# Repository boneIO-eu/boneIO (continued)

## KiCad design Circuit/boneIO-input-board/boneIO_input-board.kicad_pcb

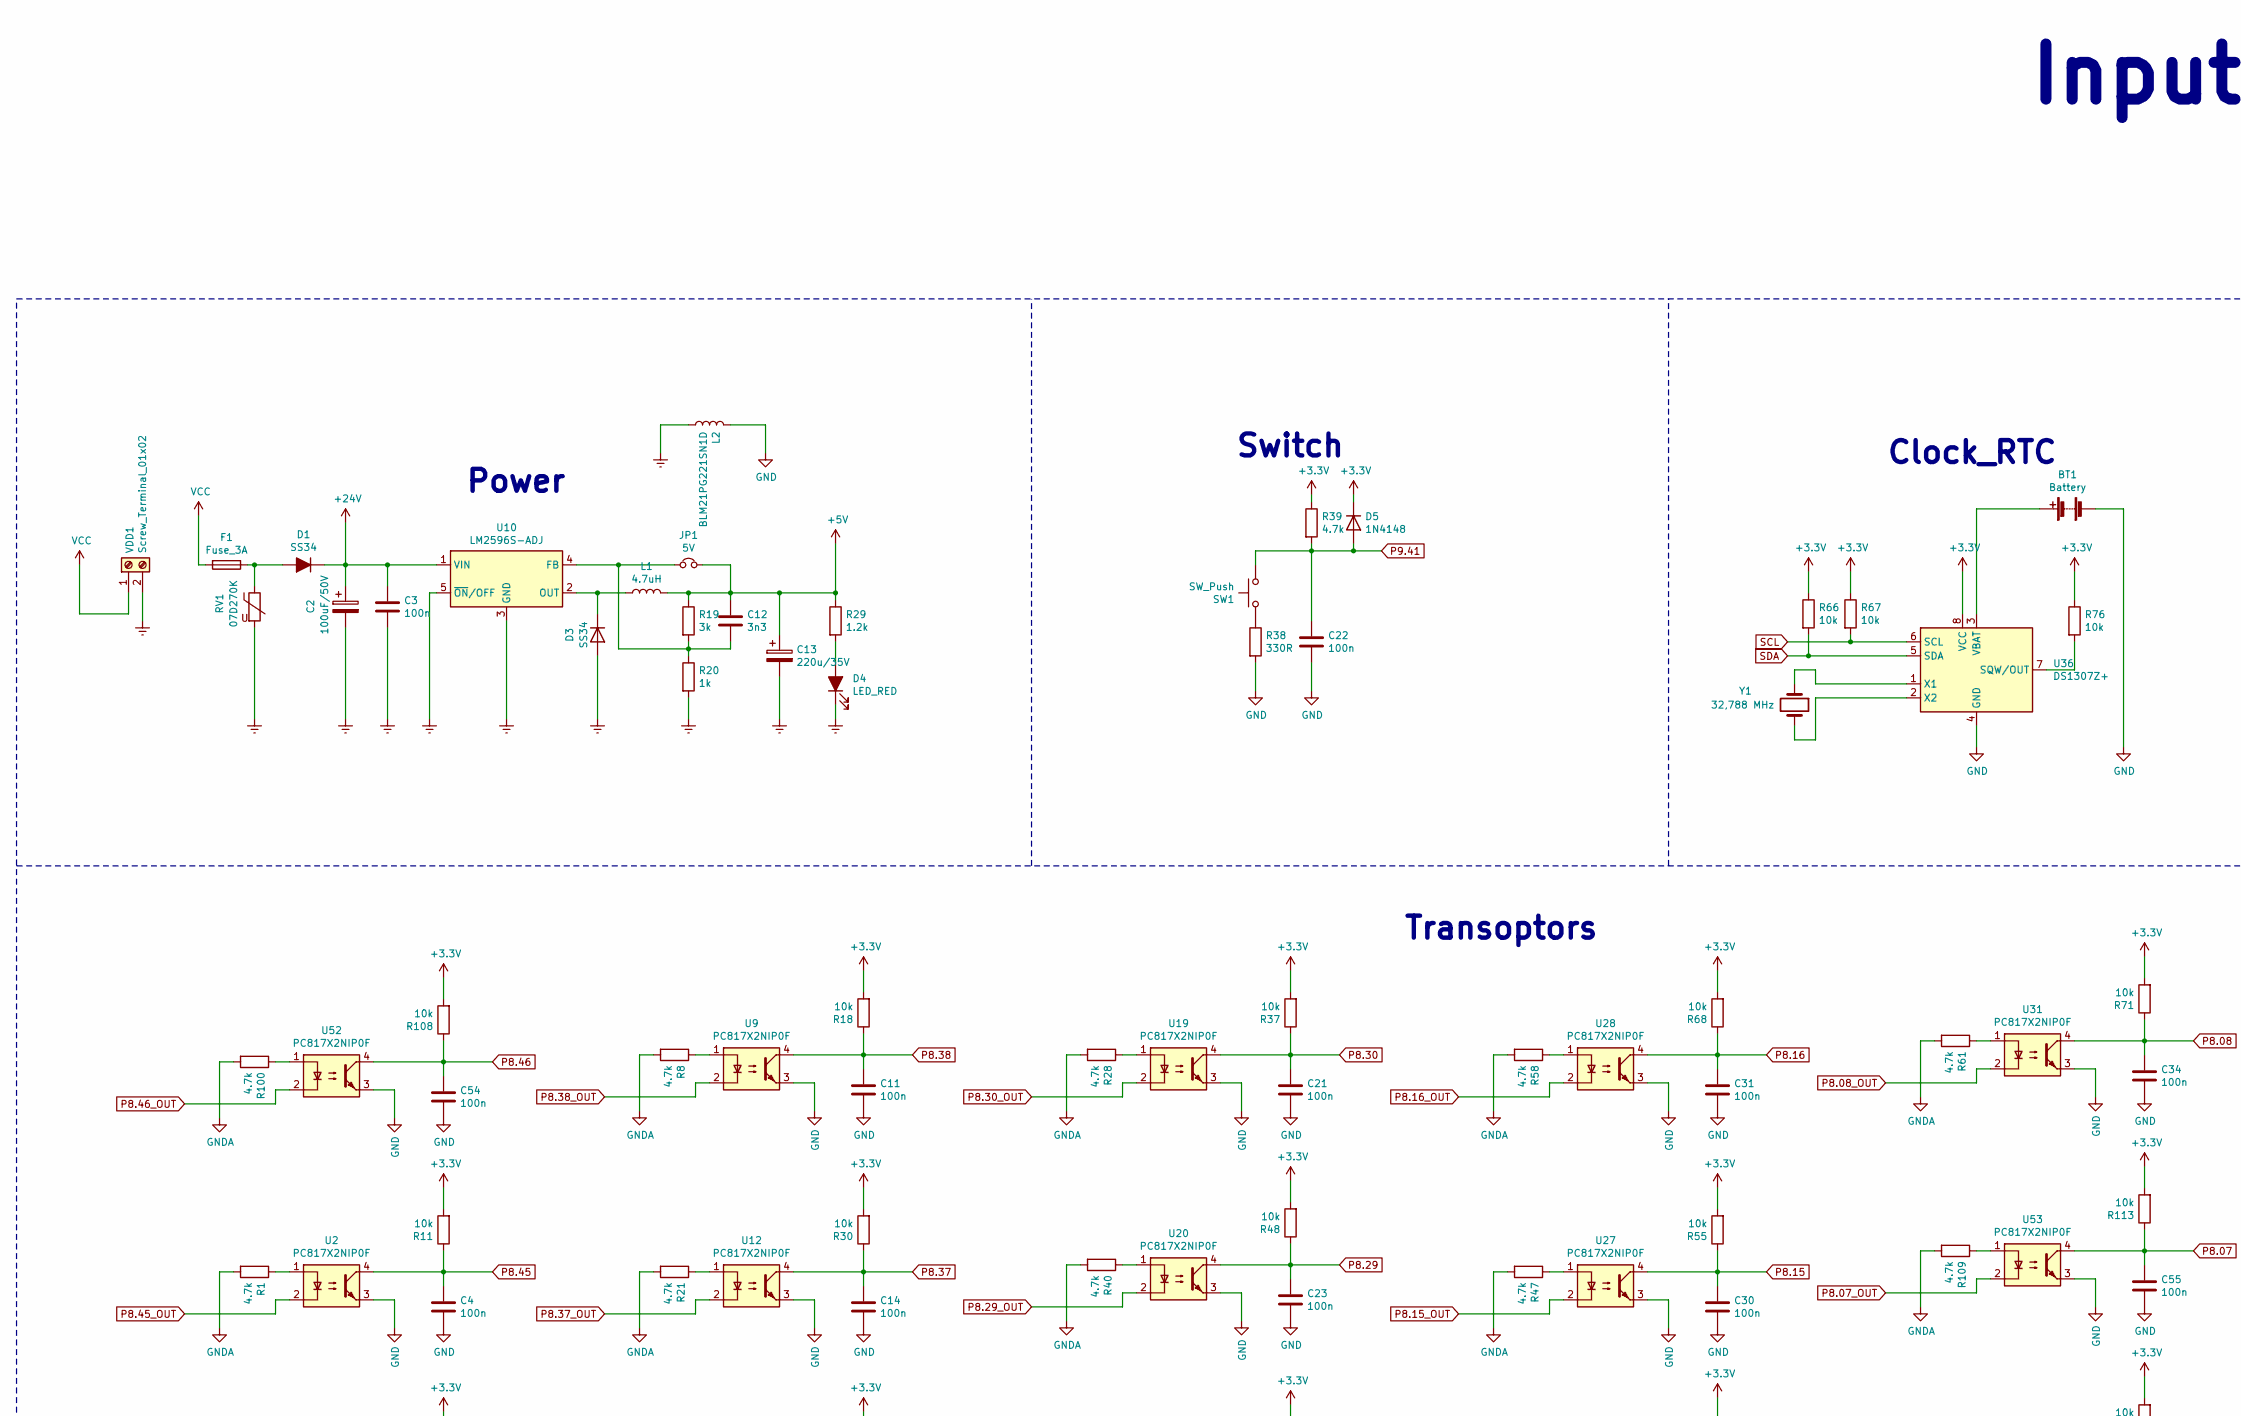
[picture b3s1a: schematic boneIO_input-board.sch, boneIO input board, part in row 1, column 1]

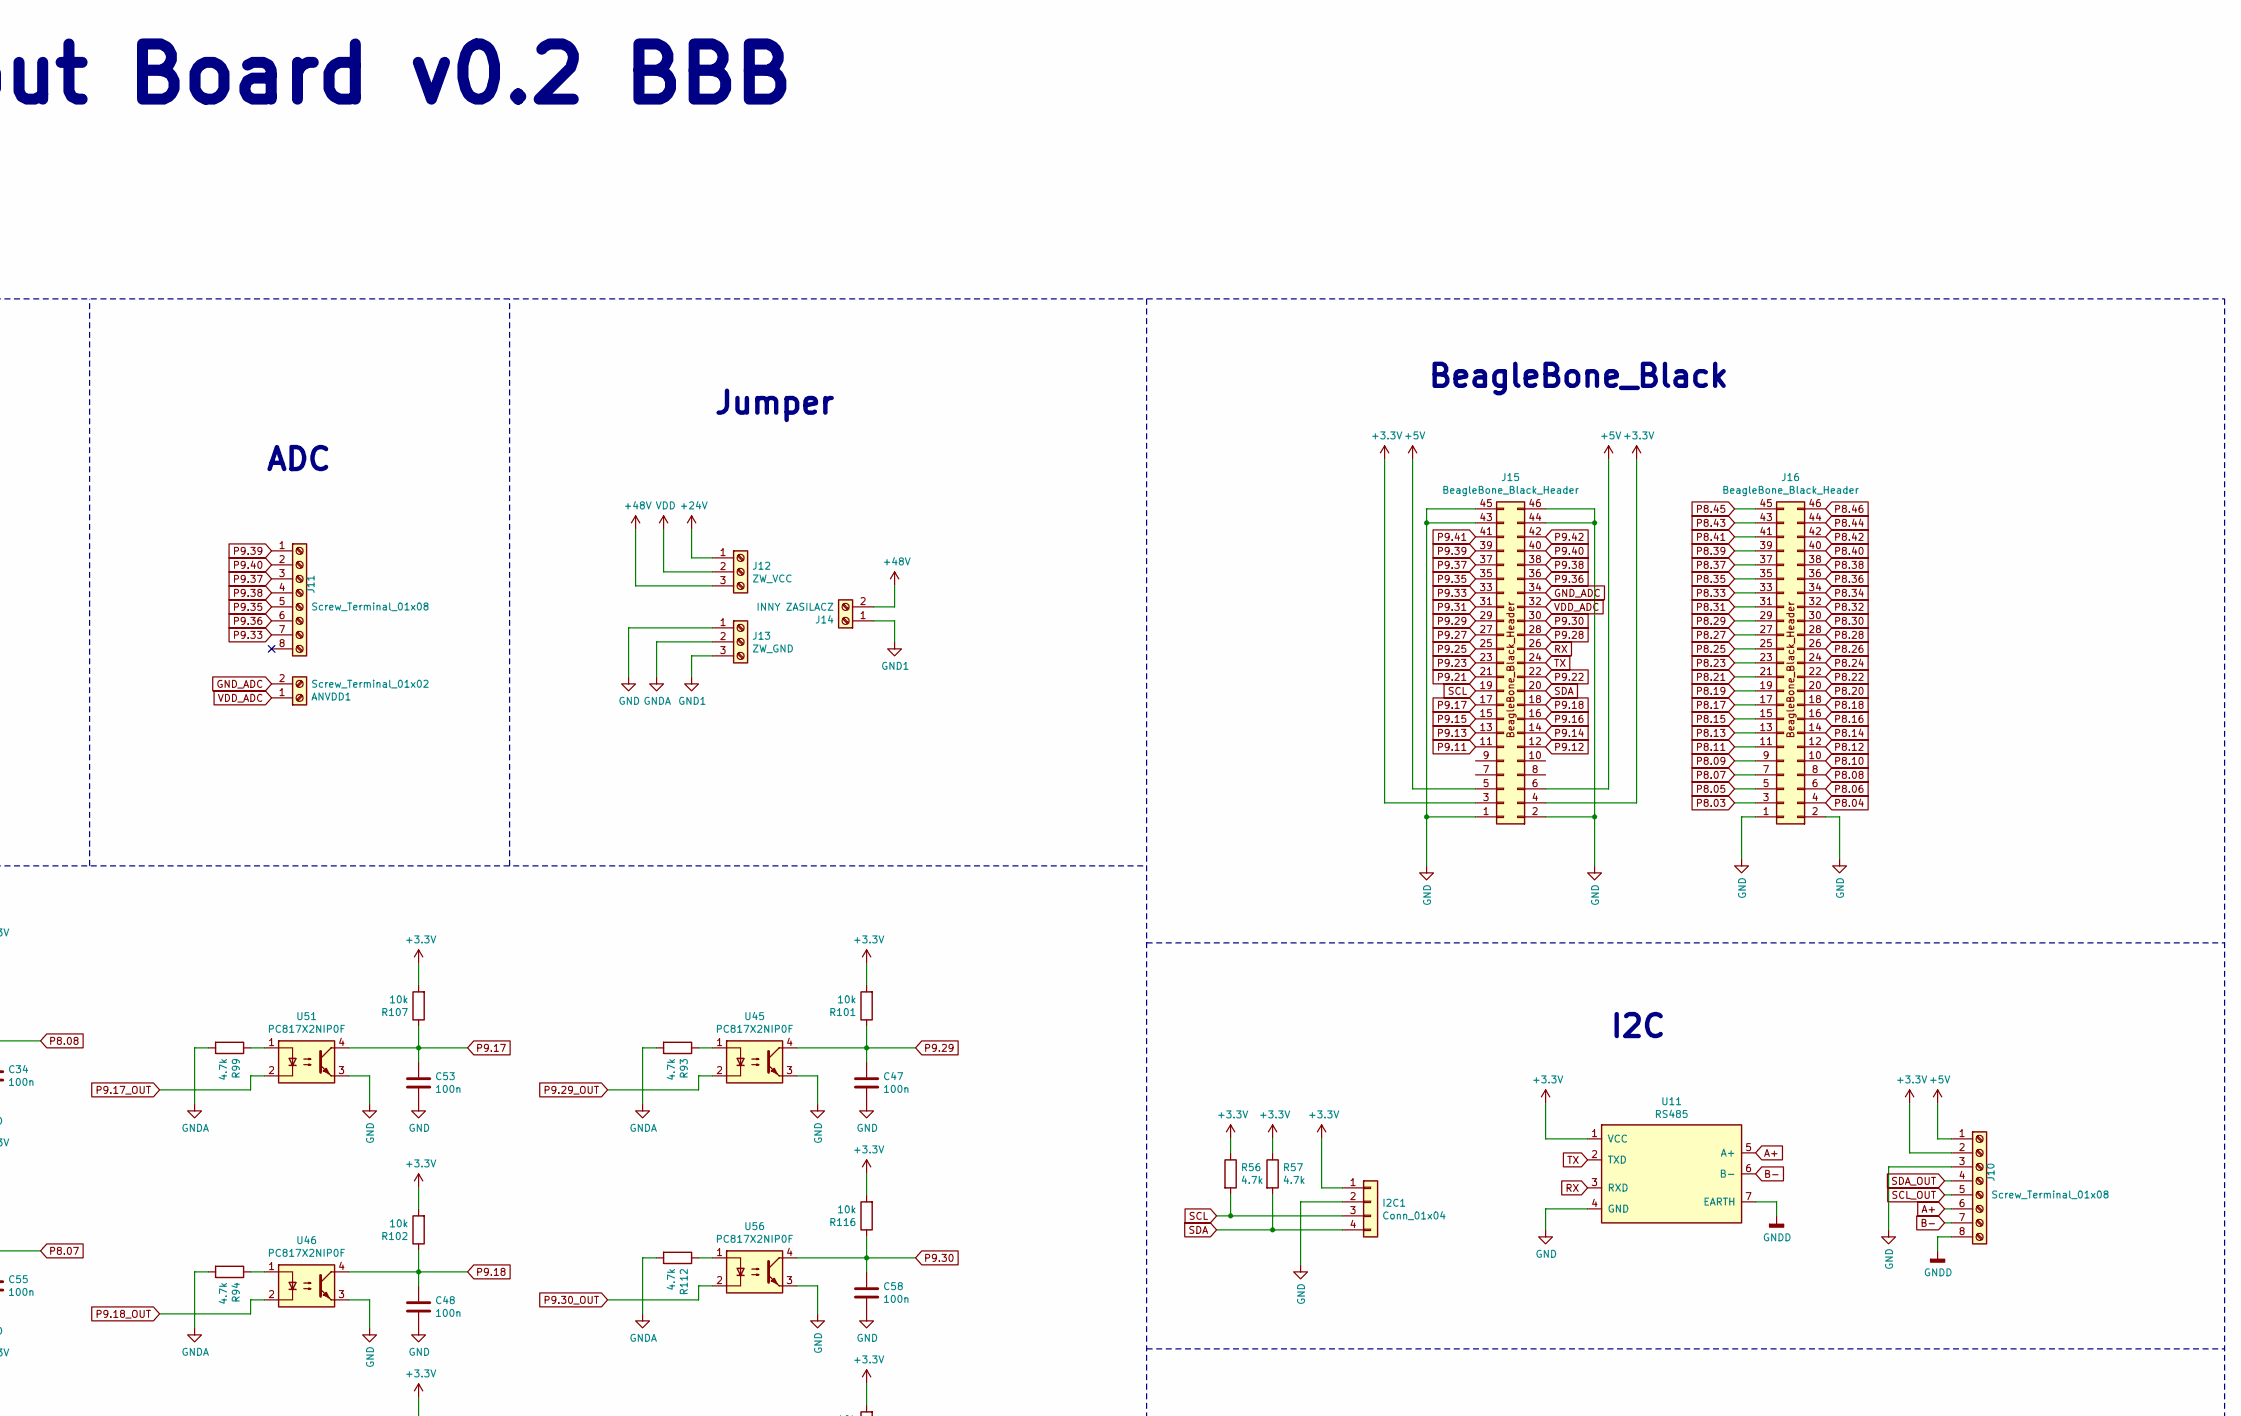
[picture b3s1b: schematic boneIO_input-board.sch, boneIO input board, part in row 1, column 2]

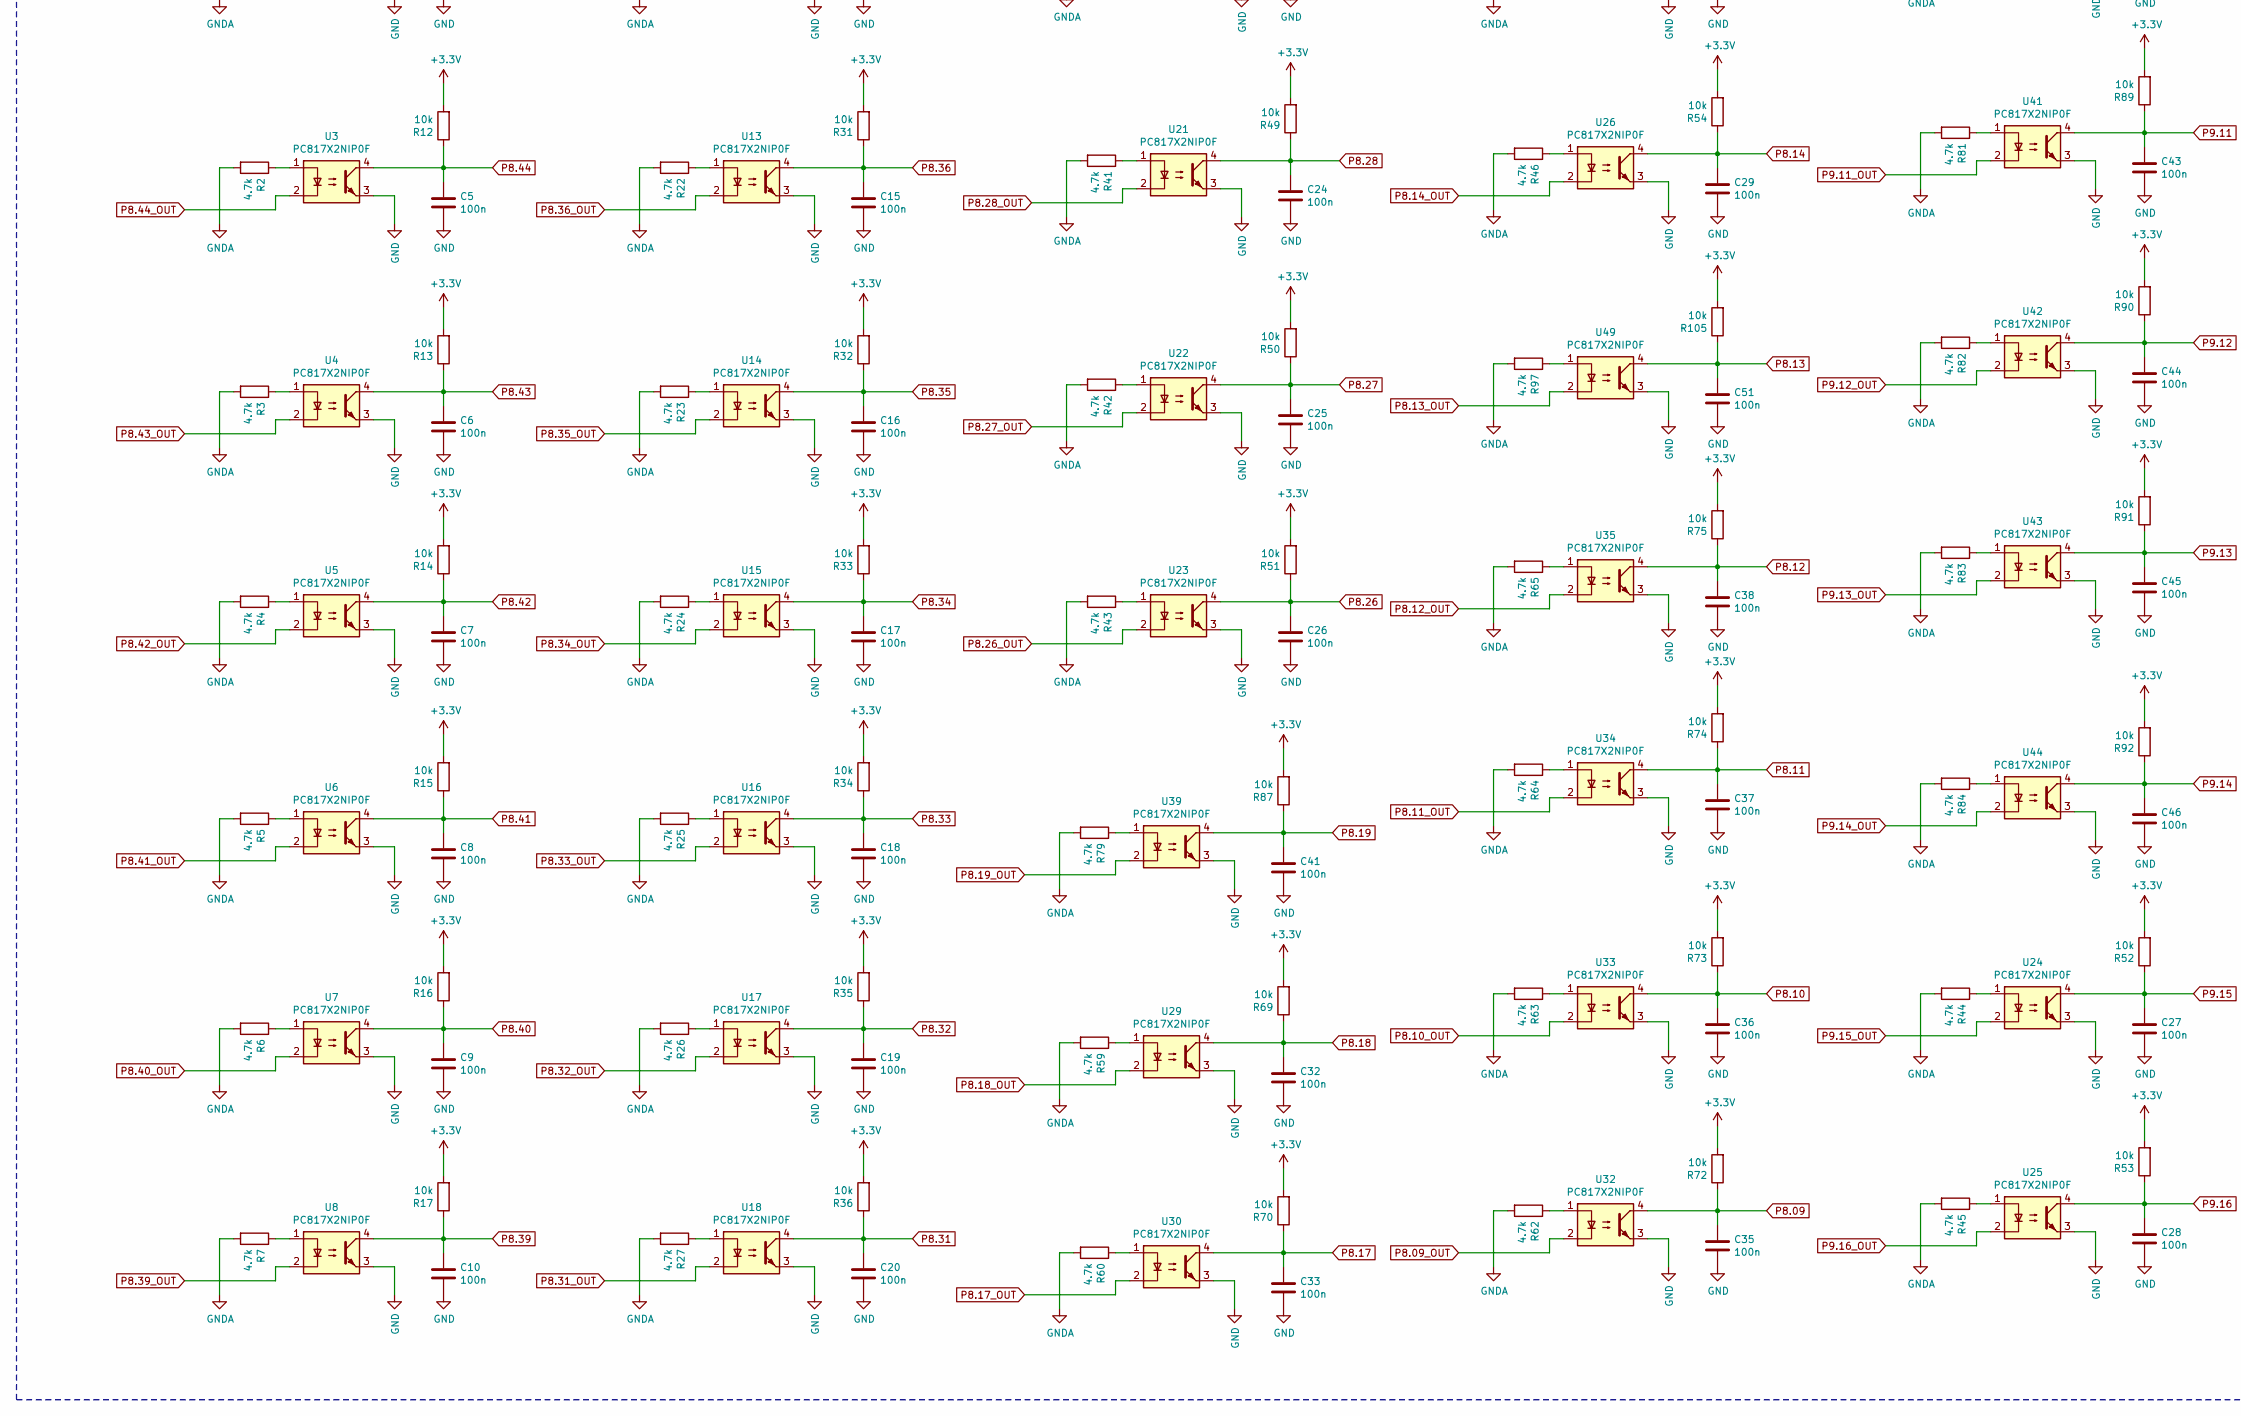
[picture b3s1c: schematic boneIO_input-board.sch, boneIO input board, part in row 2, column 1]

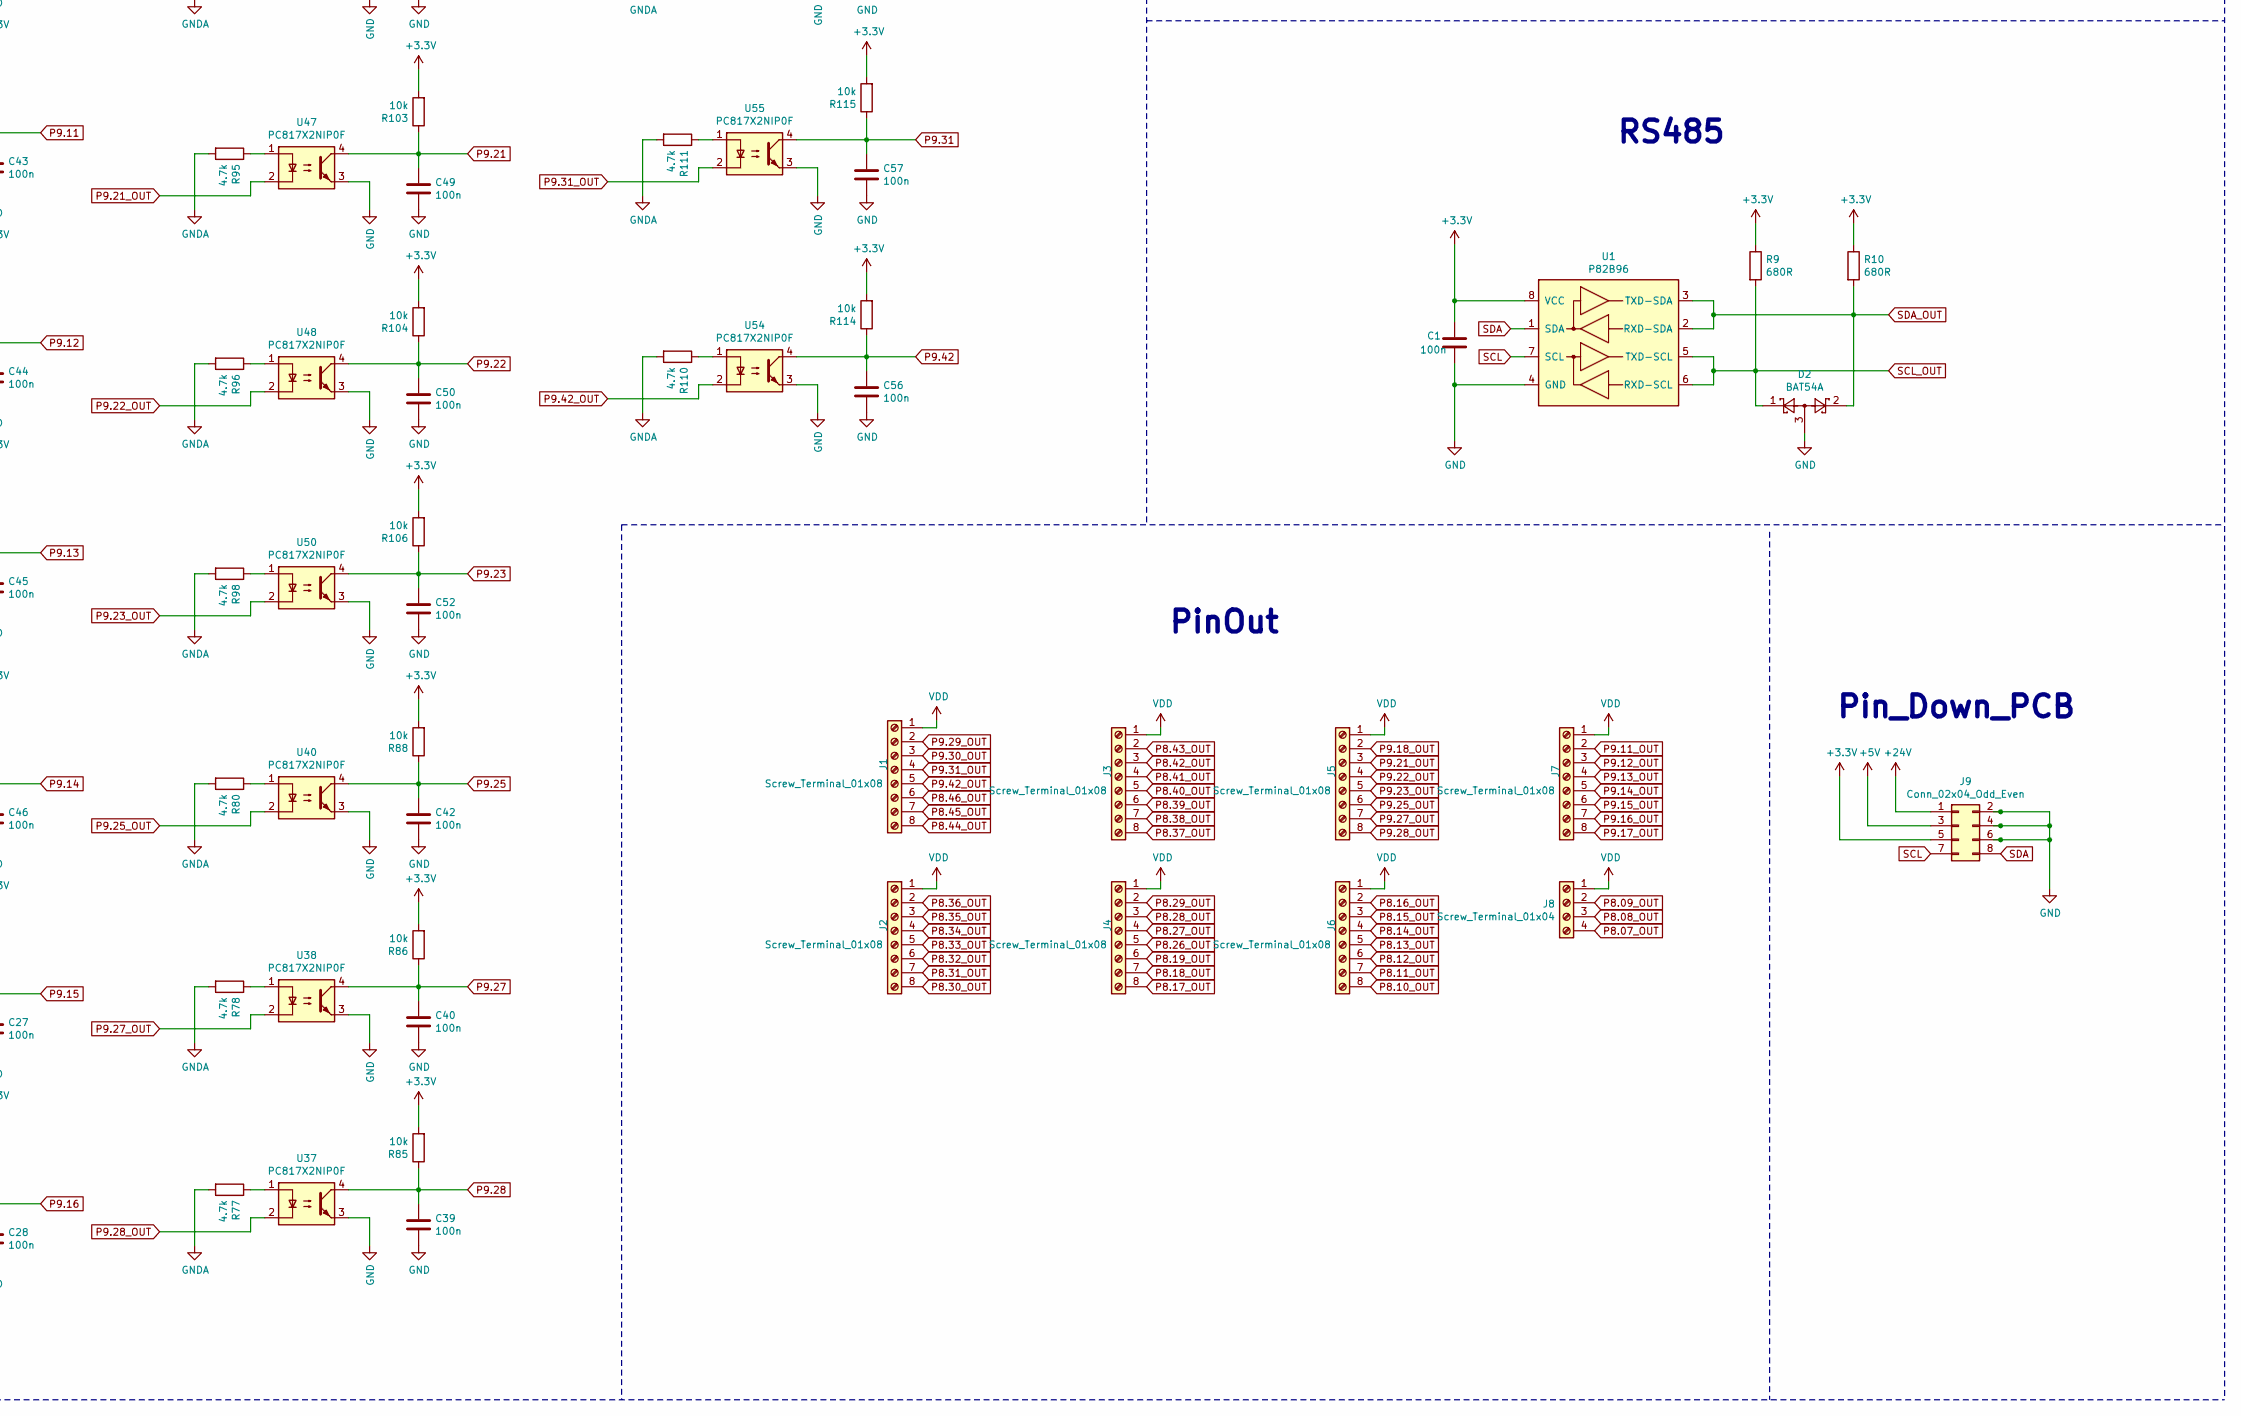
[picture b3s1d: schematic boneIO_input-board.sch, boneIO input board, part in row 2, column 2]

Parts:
ANVDD1: Screw_Terminal_01x02; Phoenix_1x02_P5.00mm_Horizontal
BT1: Battery; Battery_Panasonic_CR1220-VCN_Vertical_CircularHoles
C1, C3, C4, C5, C6, C7, C8, C9, C10, C11, C14, C15, C16, C17, C18, C19, C20, C21, C22, C23, C24, C25, C26, C27, C28, C29, C30, C31, C32, C33, C34, C35, C36, C37, C38, C39, C40, C41, C42, C43, C44, C45, C46, C47, C48, C49, C50, C51, C52, C53, C54, C55, C56, C57, C58: 100n; C_0603_1608Metric; JLCPCB C14663
C2: 100uF/50V; CP_Elec_8x10; JLCPCB C72480
C12: 3n3; C_0805_2012Metric; JLCPCB C107149
C13: 220u/35V; CP_Elec_8x10; JLCPCB C311611
D1: SS34; D_SMA; JLCPCB C64982
D2: BAT54A; SOT-23
D3: SS34; D_SMA; JLCPCB C8678
D4: LED_RED; LED_0805_2012Metric; JLCPCB C84256
D5: 1N4148; D_MiniMELF; JLCPCB C68883
F1: Fuse_3A; Fuse_2512_6332Metric; JLCPCB C136367
I2C1: Conn_01x04; PinSocket_1x04_P2.54mm_Vertical
J1, J2, J3, J4, J5, J6, J7, J10, J11: Screw_Terminal_01x08; 8pin
J8: Screw_Terminal_01x04; Phoenix_1x04_P5.00mm_Horizontal
J9: Conn_02x04_Odd_Even; PinSocket_2x04_P2.54mm_Vertical
J12: ZW_VCC; PinHeader_1x03_P2.54mm_Vertical
J13: ZW_GND; PinHeader_1x03_P2.54mm_Vertical
J14: INNY ZASILACZ; Phoenix_1x02_P5.00mm_Horizontal
J15, J16: BeagleBone_Black_Header; PinHeader_2x23_P2.54mm_Vertical
JP1: 5V; SolderJumper-2_P1.3mm_Open_Pad1.0x1.5mm
L1: 4.7uH; L_12x12mm_H6mm; JLCPCB C338848
L2: BLM21PG221SN1D; L_0805_2012Metric; JLCPCB C85840
R1, R2, R3, R4, R5, R6, R7, R8, R21, R22, R23, R24, R25, R26, R27, R28, R39, R40, R41, R42, R43, R44, R45, R46, R47, R56, R57, R58, R59, R60, R61, R62, R63, R64, R65, R77, R78, R79, R80, R81, R82, R83, R84, R93, R94, R95, R96, R97, R98, R99, R100, R109, R110, R111, R112: 4.7k; R_0603_1608Metric; JLCPCB C237118
R9, R10: 680R; R_0603_1608Metric; JLCPCB C269704
R11, R12, R13, R14, R15, R16, R17, R18, R30, R31, R32, R33, R34, R35, R36, R37, R48, R49, R50, R51, R52, R53, R54, R55, R66, R67, R68, R69, R70, R71, R72, R73, R74, R75, R76, R85, R86, R87, R88, R89, R90, R91, R92, R101, R102, R103, R104, R105, R106, R107, R108, R113, R114, R115, R116: 10k; R_0603_1608Metric; JLCPCB C238881
R19: 3k; R_0603_1608Metric; JLCPCB C126358
R20: 1k; R_0603_1608Metric; JLCPCB C269704
R29: 1.2k; R_0603_1608Metric; JLCPCB C269704
R38: 330R; R_0603_1608Metric; JLCPCB C101062
RV1: 07D270K; RV_Disc_D7mm_W3.5mm_P5mm; JLCPCB C317745
SW1: SW_Push; SW_PUSH_6mm_H13mm
U1: P82B96; SO-8_3.9x4.9mm_P1.27mm; JLCPCB C32103
U2, U3, U4, U5, U6, U7, U8, U9, U12, U13, U14, U15, U16, U17, U18, U19, U20, U21, U22, U23, U24, U25, U26, U27, U28, U29, U30, U31, U32, U33, U34, U35, U37, U38, U39, U40, U41, U42, U43, U44, U45, U46, U47, U48, U49, U50, U51, U52, U53, U54, U55, U56: PC817X2NIP0F; SOT254P975X400-4N; JLCPCB C6649
U10: LM2596S-ADJ; TO-263-5_TabPin3
U11: RS485; RS485_moduleTTL
U36: DS1307Z+; SOIC-8_3.9x4.9mm_P1.27mm; JLCPCB C26858
VDD1: Screw_Terminal_01x02; Phoenix_1x02_P5.00mm_Horizontal
Y1: 32,788 MHz; Crystal_C26-LF_D2.1mm_L6.5mm_Horizontal

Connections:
+3V3: C1.1, D5.1 (K), I2C1.1, J9.5, J10.2, J15.3, J15.4, R9.1, R10.1, R11.2, R12.2, R13.2, R14.2, R15.2, R16.2, R17.2, R18.2, R30.2, R31.2, R32.2, R33.2, R34.2, R35.2, R36.2, R37.2, R39.1, R48.2, R49.2, R50.2, R51.2, R52.2, R53.2, R54.2, R55.2, R56.1, R57.1, R66.1, R67.1, R68.2, R69.2, R70.2, R71.2, R72.2, R73.2, R74.2, R75.2, R76.1, R85.2, R86.2, R87.2, R88.2, R89.2, R90.2, R91.2, R92.2, R101.2, R102.2, R103.2, R104.2, R105.2, R106.2, R107.2, R108.2, R113.2, R114.2, R115.2, R116.2, U1.8 (VCC), U11.1 (VCC), U36.8 (VCC)
+5V: C12.1, C13.1, J9.3, J10.1, J15.5, J15.6, JP1.2, L1.2, R19.1, R29.1
+24V: C2.1, C3.1, D1.1 (K), J9.1, J12.1, U10.1 (VIN)
+48V: J12.3, J14.2
A+: J10.6, U11.5 (A+)
B-: J10.7, U11.6 (B-)
Earth: C2.2, C3.2, C13.2, D3.2 (A), D4.1 (K), L2.1, R20.2, RV1.2, U10.3 (GND), U10.5 (~ON~/OFF), VDD1.2
GND: BT1.2 (-), C1.2, C4.2, C5.2, C6.2, C7.2, C8.2, C9.2, C10.2, C11.2, C14.2, C15.2, C16.2, C17.2, C18.2, C19.2, C20.2, C21.2, C22.2, C23.2, C24.2, C25.2, C26.2, C27.2, C28.2, C29.2, C30.2, C31.2, C32.2, C33.2, C34.2, C35.2, C36.2, C37.2, C38.2, C39.2, C40.2, C41.2, C42.2, C43.2, C44.2, C45.2, C46.2, C47.2, C48.2, C49.2, C50.2, C51.2, C52.2, C53.2, C54.2, C55.2, C56.2, C57.2, C58.2, D2.3, I2C1.2, J9.2, J9.4, J9.6, J10.3, J13.1, J15.1, J15.2, J15.43, J15.44, J15.45, J15.46, J16.1, J16.2, L2.2, R38.2, U1.4 (GND), U2.3, U3.3, U4.3, U5.3, U6.3, U7.3, U8.3, U9.3, U11.4 (GND), U12.3, U13.3, U14.3, U15.3, U16.3, U17.3, U18.3, U19.3, U20.3, U21.3, U22.3, U23.3, U24.3, U25.3, U26.3, U27.3, U28.3, U29.3, U30.3, U31.3, U32.3, U33.3, U34.3, U35.3, U36.4 (GND), U37.3, U38.3, U39.3, U40.3, U41.3, U42.3, U43.3, U44.3, U45.3, U46.3, U47.3, U48.3, U49.3, U50.3, U51.3, U52.3, U53.3, U54.3, U55.3, U56.3
GND1: J13.3, J14.1
GNDA: J13.2, R1.2, R2.2, R3.2, R4.2, R5.2, R6.2, R7.2, R8.2, R21.2, R22.2, R23.2, R24.2, R25.2, R26.2, R27.2, R28.2, R40.2, R41.2, R42.2, R43.2, R44.2, R45.2, R46.2, R47.2, R58.2, R59.2, R60.2, R61.2, R62.2, R63.2, R64.2, R65.2, R77.2, R78.2, R79.2, R80.2, R81.2, R82.2, R83.2, R84.2, R93.2, R94.2, R95.2, R96.2, R97.2, R98.2, R99.2, R100.2, R109.2, R110.2, R111.2, R112.2
GNDD: J10.8, U11.7 (EARTH)
GND_ADC: ANVDD1.2, J15.34
unnamed: BT1.1 (+), U36.3 (VBAT)
unnamed: C12.2, JP1.1, R19.2, R20.1, U10.4 (FB)
unnamed: D1.2 (A), F1.1, RV1.1
unnamed: D3.1 (K), L1.1, U10.2 (OUT)
unnamed: D4.2 (A), R29.2
unnamed: R1.1, U2.1
unnamed: R2.1, U3.1
unnamed: R3.1, U4.1
unnamed: R4.1, U5.1
unnamed: R5.1, U6.1
unnamed: R6.1, U7.1
unnamed: R7.1, U8.1
unnamed: R8.1, U9.1
unnamed: R21.1, U12.1
unnamed: R22.1, U13.1
unnamed: R23.1, U14.1
unnamed: R24.1, U15.1
unnamed: R25.1, U16.1
unnamed: R26.1, U17.1
unnamed: R27.1, U18.1
unnamed: R28.1, U19.1
unnamed: R38.1, SW1.1
unnamed: R40.1, U20.1
unnamed: R41.1, U21.1
unnamed: R42.1, U22.1
unnamed: R43.1, U23.1
unnamed: R44.1, U24.1
unnamed: R45.1, U25.1
unnamed: R46.1, U26.1
unnamed: R47.1, U27.1
unnamed: R58.1, U28.1
unnamed: R59.1, U29.1
unnamed: R60.1, U30.1
unnamed: R61.1, U31.1
unnamed: R62.1, U32.1
unnamed: R63.1, U33.1
unnamed: R64.1, U34.1
unnamed: R65.1, U35.1
unnamed: R76.2, U36.7 (SQW/OUT)
unnamed: R77.1, U37.1
unnamed: R78.1, U38.1
unnamed: R79.1, U39.1
unnamed: R80.1, U40.1
unnamed: R81.1, U41.1
unnamed: R82.1, U42.1
unnamed: R83.1, U43.1
unnamed: R84.1, U44.1
unnamed: R93.1, U45.1
unnamed: R94.1, U46.1
unnamed: R95.1, U47.1
unnamed: R96.1, U48.1
unnamed: R97.1, U49.1
unnamed: R98.1, U50.1
unnamed: R99.1, U51.1
unnamed: R100.1, U52.1
unnamed: R109.1, U53.1
unnamed: R110.1, U54.1
unnamed: R111.1, U55.1
unnamed: R112.1, U56.1
unnamed: U36.1 (X1), Y1.1
unnamed: U36.2 (X2), Y1.2
P8.03: J16.3
P8.04: J16.4
P8.05: J16.5
P8.06: J16.6
P8.07: C55.1, J16.7, R113.1, U53.4
P8.07_OUT: J8.4, U53.2
P8.08: C34.1, J16.8, R71.1, U31.4
P8.08_OUT: J8.3, U31.2
P8.09: C35.1, J16.9, R72.1, U32.4
P8.09_OUT: J8.2, U32.2
P8.10: C36.1, J16.10, R73.1, U33.4
P8.10_OUT: J6.8, U33.2
P8.11: C37.1, J16.11, R74.1, U34.4
P8.11_OUT: J6.7, U34.2
P8.12: C38.1, J16.12, R75.1, U35.4
P8.12_OUT: J6.6, U35.2
P8.13: C51.1, J16.13, R105.1, U49.4
P8.13_OUT: J6.5, U49.2
P8.14: C29.1, J16.14, R54.1, U26.4
P8.14_OUT: J6.4, U26.2
P8.15: C30.1, J16.15, R55.1, U27.4
P8.15_OUT: J6.3, U27.2
P8.16: C31.1, J16.16, R68.1, U28.4
P8.16_OUT: J6.2, U28.2
P8.17: C33.1, J16.17, R70.1, U30.4
P8.17_OUT: J4.8, U30.2
P8.18: C32.1, J16.18, R69.1, U29.4
P8.18_OUT: J4.7, U29.2
P8.19: C41.1, J16.19, R87.1, U39.4
P8.19_OUT: J4.6, U39.2
P8.20: J16.20
P8.21: J16.21
P8.22: J16.22
P8.23: J16.23
P8.24: J16.24
P8.25: J16.25
P8.26: C26.1, J16.26, R51.1, U23.4
P8.26_OUT: J4.5, U23.2
P8.27: C25.1, J16.27, R50.1, U22.4
P8.27_OUT: J4.4, U22.2
P8.28: C24.1, J16.28, R49.1, U21.4
P8.28_OUT: J4.3, U21.2
P8.29: C23.1, J16.29, R48.1, U20.4
P8.29_OUT: J4.2, U20.2
P8.30: C21.1, J16.30, R37.1, U19.4
P8.30_OUT: J2.8, U19.2
P8.31: C20.1, J16.31, R36.1, U18.4
P8.31_OUT: J2.7, U18.2
P8.32: C19.1, J16.32, R35.1, U17.4
P8.32_OUT: J2.6, U17.2
P8.33: C18.1, J16.33, R34.1, U16.4
P8.33_OUT: J2.5, U16.2
P8.34: C17.1, J16.34, R33.1, U15.4
P8.34_OUT: J2.4, U15.2
P8.35: C16.1, J16.35, R32.1, U14.4
P8.35_OUT: J2.3, U14.2
P8.36: C15.1, J16.36, R31.1, U13.4
P8.36_OUT: J2.2, U13.2
P8.37: C14.1, J16.37, R30.1, U12.4
P8.37_OUT: J3.8, U12.2
P8.38: C11.1, J16.38, R18.1, U9.4
P8.38_OUT: J3.7, U9.2
P8.39: C10.1, J16.39, R17.1, U8.4
P8.39_OUT: J3.6, U8.2
P8.40: C9.1, J16.40, R16.1, U7.4
P8.40_OUT: J3.5, U7.2
P8.41: C8.1, J16.41, R15.1, U6.4
P8.41_OUT: J3.4, U6.2
P8.42: C7.1, J16.42, R14.1, U5.4
P8.42_OUT: J3.3, U5.2
P8.43: C6.1, J16.43, R13.1, U4.4
P8.43_OUT: J3.2, U4.2
P8.44: C5.1, J16.44, R12.1, U3.4
P8.44_OUT: J1.8, U3.2
P8.45: C4.1, J16.45, R11.1, U2.4
P8.45_OUT: J1.7, U2.2
P8.46: C54.1, J16.46, R108.1, U52.4
P8.46_OUT: J1.6, U52.2
P9.11: C43.1, J15.11, R89.1, U41.4
P9.11_OUT: J7.2, U41.2
P9.12: C44.1, J15.12, R90.1, U42.4
P9.12_OUT: J7.3, U42.2
P9.13: C45.1, J15.13, R91.1, U43.4
P9.13_OUT: J7.4, U43.2
P9.14: C46.1, J15.14, R92.1, U44.4
P9.14_OUT: J7.5, U44.2
P9.15: C27.1, J15.15, R52.1, U24.4
P9.15_OUT: J7.6, U24.2
P9.16: C28.1, J15.16, R53.1, U25.4
P9.16_OUT: J7.7, U25.2
P9.17: C53.1, J15.17, R107.1, U51.4
P9.17_OUT: J7.8, U51.2
P9.18: C48.1, J15.18, R102.1, U46.4
P9.18_OUT: J5.2, U46.2
P9.21: C49.1, J15.21, R103.1, U47.4
P9.21_OUT: J5.3, U47.2
P9.22: C50.1, J15.22, R104.1, U48.4
P9.22_OUT: J5.4, U48.2
P9.23: C52.1, J15.23, R106.1, U50.4
P9.23_OUT: J5.5, U50.2
P9.25: C42.1, J15.25, R88.1, U40.4
P9.25_OUT: J5.6, U40.2
P9.27: C40.1, J15.27, R86.1, U38.4
P9.27_OUT: J5.7, U38.2
P9.28: C39.1, J15.28, R85.1, U37.4
P9.28_OUT: J5.8, U37.2
P9.29: C47.1, J15.29, R101.1, U45.4
P9.29_OUT: J1.2, U45.2
P9.30: C58.1, J15.30, R116.1, U56.4
P9.30_OUT: J1.3, U56.2
P9.31: C57.1, J15.31, R115.1, U55.4
P9.31_OUT: J1.4, U55.2
P9.33: J11.7, J15.33
P9.35: J11.5, J15.35
P9.36: J11.6, J15.36
P9.37: J11.3, J15.37
P9.38: J11.4, J15.38
P9.39: J11.1, J15.39
P9.40: J11.2, J15.40
P9.41: C22.1, D5.2 (A), J15.41, R39.2, SW1.2
P9.42: C56.1, J15.42, R114.1, U54.4
P9.42_OUT: J1.5, U54.2
RX: J15.26, U11.3 (RXD)
SCL: I2C1.3, J9.7, J15.19, R56.2, R67.2, U1.7 (SCL), U36.6 (SCL)
SCL_OUT: D2.1, J10.5, R9.2, U1.5 (TXD-SCL), U1.6 (RXD-SCL)
SDA: I2C1.4, J9.8, J15.20, R57.2, R66.2, U1.1 (SDA), U36.5 (SDA)
SDA_OUT: D2.2, J10.4, R10.2, U1.2 (RXD-SDA), U1.3 (TXD-SDA)
TX: J15.24, U11.2 (TXD)
VCC: F1.2, VDD1.1
VDD: J1.1, J2.1, J3.1, J4.1, J5.1, J6.1, J7.1, J8.1, J12.2
VDD_ADC: ANVDD1.1, J15.32

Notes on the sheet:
Power
Clock_RTC
I2C
Switch
BeagleBone_Black
Pin_Down_PCB
RS485
PinOut
Transoptors
ADC
Jumper
Input Board v0.2 BBB

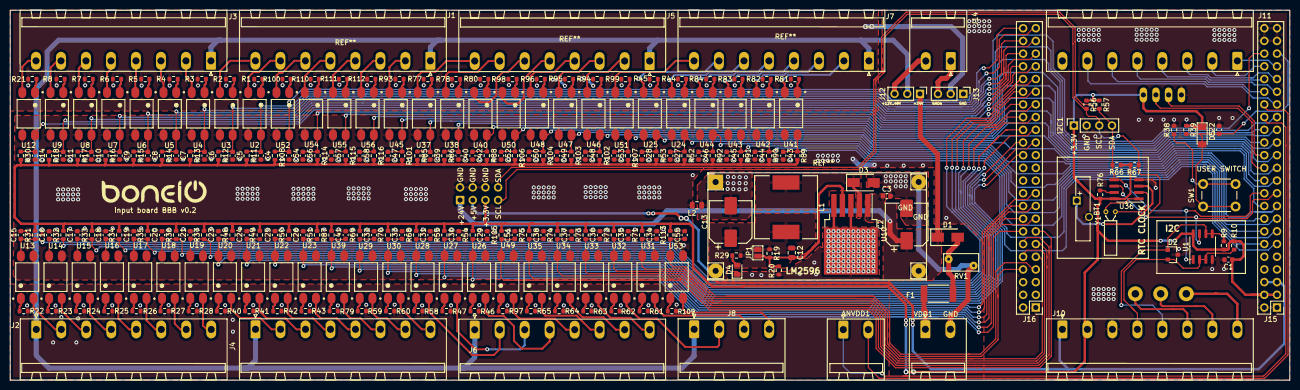
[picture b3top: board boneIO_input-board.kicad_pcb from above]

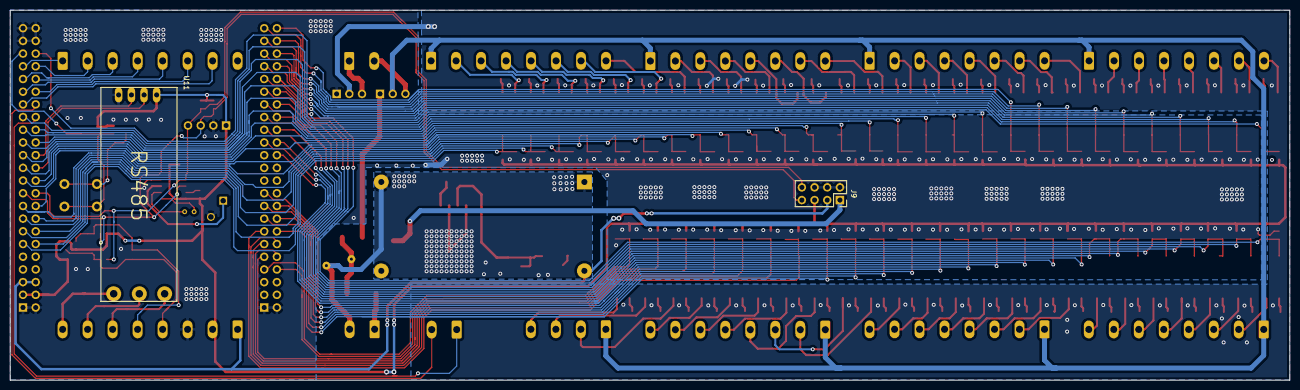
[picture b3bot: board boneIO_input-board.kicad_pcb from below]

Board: 2 copper layers, 256.0 x 74.0 mm, 262 parts (2 on the bottom side), 194 nets.
